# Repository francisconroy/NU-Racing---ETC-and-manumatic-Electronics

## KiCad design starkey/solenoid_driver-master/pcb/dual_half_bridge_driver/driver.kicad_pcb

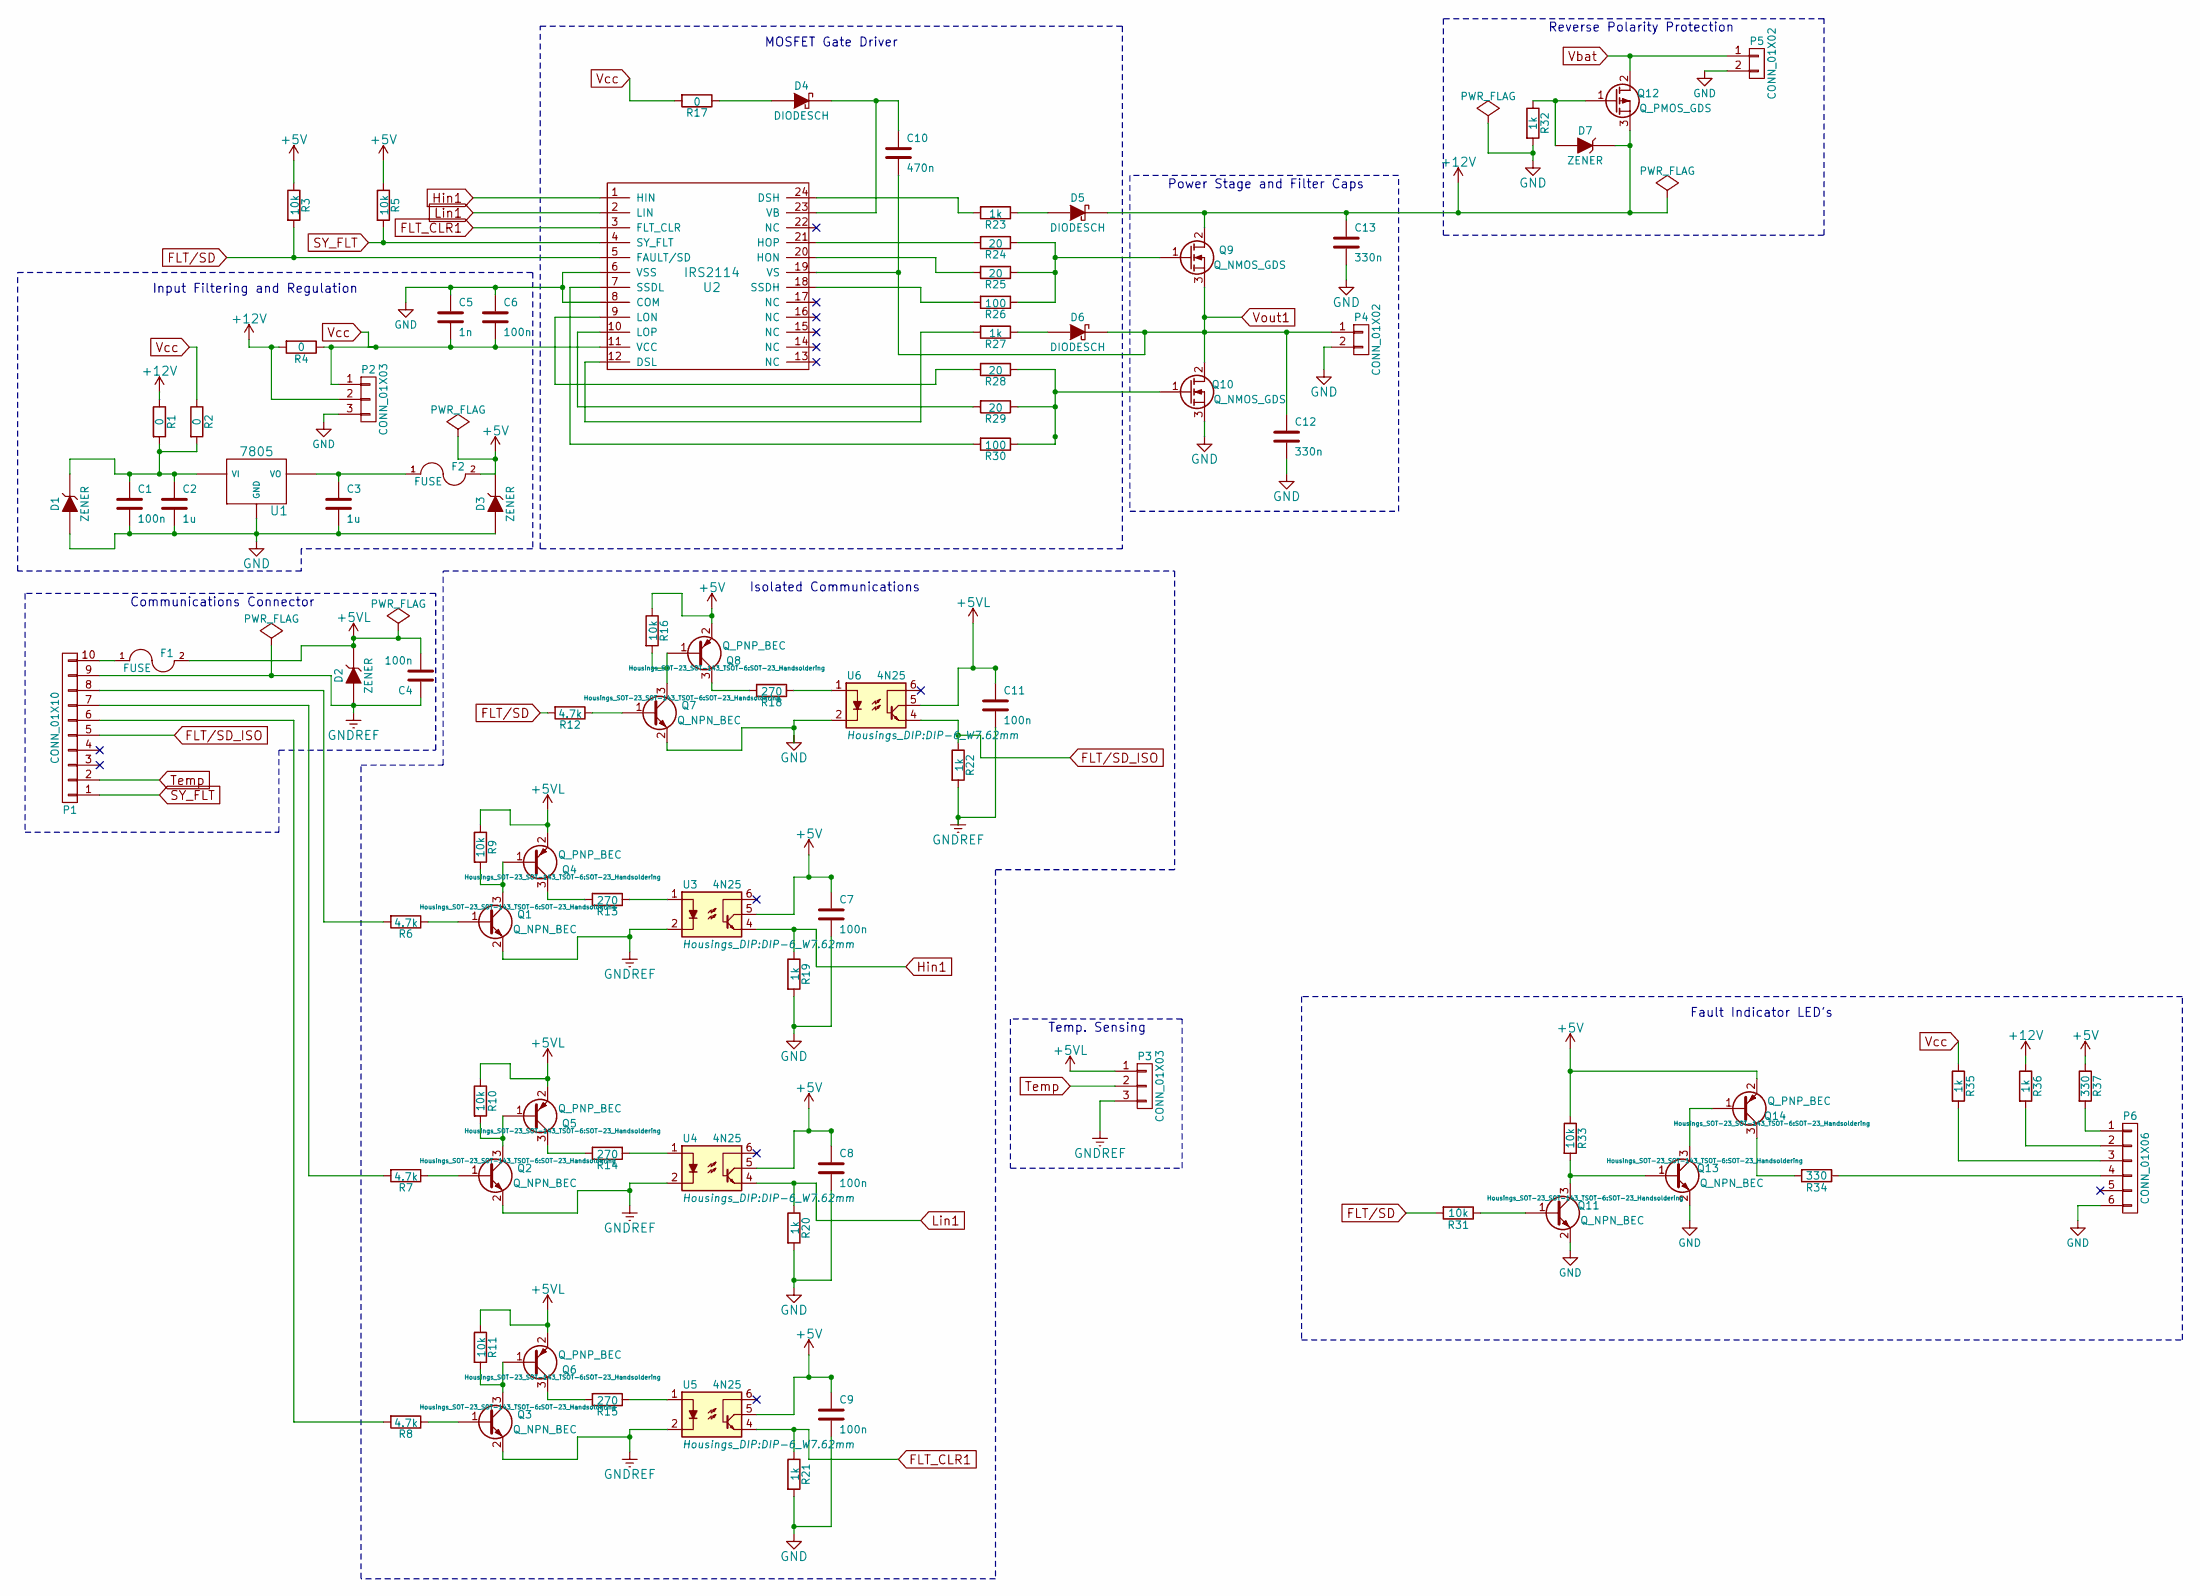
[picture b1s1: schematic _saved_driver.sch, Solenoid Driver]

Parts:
C1, C4, C6, C7, C8, C9, C11: 100n; C_1206_HandSoldering
C2, C3: 1u; C_1206_HandSoldering
C5: 1n; C_1206_HandSoldering
C10: 470n; C_1206_HandSoldering
C12: 330n; C_Rect_L32_W15_P27
C13: 330n; C_Rect_L18_W6_H12_P15
D1, D2, D3, D7: ZENER; SMD-1206_Pol
D4, D5, D6: DIODESCH; SMD-1206_Pol
F1, F2: FUSE; R_1206_HandSoldering
P1: CONN_01X10; Pin_Header_Straight_1x10
P2, P3: CONN_01X03; Pin_Header_Straight_1x03
P4: CONN_01X02; Pin_Header_Straight_1x02
P5: CONN_01X02; Crimp_Connector_2
P6: CONN_01X06; Pin_Header_Straight_1x06
Q1, Q2, Q3, Q7, Q11, Q13: Q_NPN_BEC; SOT-23_Handsoldering
Q4, Q5, Q6, Q8, Q14: Q_PNP_BEC; SOT-23_Handsoldering
Q9, Q10: Q_NMOS_GDS; TO-247_Vertical_Neutral123
Q12: Q_PMOS_GDS; TO-220_Neutral123_Vertical
R1, R2, R4, R17: 0; R_1206_HandSoldering
R3, R5, R9, R10, R11, R16, R31, R33: 10k; R_1206_HandSoldering
R6, R7, R8, R12: 4.7k; R_1206_HandSoldering
R13, R14, R15, R18: 270; R_1206_HandSoldering
R19, R20, R21, R22, R23, R27, R32, R35, R36: 1k; R_1206_HandSoldering
R24, R25, R28, R29: 20; R_1206_HandSoldering
R26, R30: 100; R_1206_HandSoldering
R34, R37: 330; R_1206_HandSoldering
U1: 7805; D-Pak_TO252AA
U2: IRS2114; SSOP-24_5.3x8.2mm_Pitch0.65mm
U3, U4, U5, U6: 4N25; DIP-6_W7.62mm

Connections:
+5V: C7.1, C8.1, C9.1, D3.2 (K), F2.2, Q8.2 (E), Q14.2 (E), R3.1, R5.1, R16.1, R33.1, R37.1, U3.5, U4.5, U5.5; also elsewhere on the board
+5VL: C4.2, C11.1, D2.2 (K), F1.2, P3.1, Q4.2 (E), Q5.2 (E), Q6.2 (E), R9.1, R10.1, R11.1, U6.5
+12V: C13.1, D5.2 (K), D7.2 (K), P2.2, Q9.2 (D), Q12.3 (S), R1.1, R4.2, R36.1
FLT/SD: R3.2, R12.2, R31.2, U2.5 (FAULT/SD)
FLT/SD_ISO: P1.5, R22.1, U6.4
FLT_CLR1: R21.1, U2.3 (FLT_CLR), U5.4
GNDREF: C4.1, C11.2, D2.1 (A), P1.9, P3.3, Q1.2 (E), Q2.2 (E), Q3.2 (E), R22.2, U3.2, U4.2, U5.2
Hin1: R19.1, U2.1 (HIN), U3.4
Lin1: R20.1, U2.2 (LIN), U4.4
unnamed: C1.1, C2.1, D1.2 (K), R1.2, R2.2, U1.1, U1.VI
unnamed: C3.1, F2.1, U1.3, U1.VO
unnamed: C10.1, D4.2 (K), U2.23 (VB)
unnamed: D4.1 (A), R17.1
unnamed: D5.1 (A), R23.1
unnamed: D6.1 (A), R27.1
unnamed: D7.1 (A), Q12.1 (G), R32.1
unnamed: F1.1, P1.10
unnamed: P1.6, R8.2
unnamed: P1.7, R7.2
unnamed: P1.8, R6.2
unnamed: P6.1, R37.2
unnamed: P6.2, R36.2
unnamed: P6.3, R35.2
unnamed: P6.4, R34.1
unnamed: Q1.1 (B), R6.1
unnamed: Q1.3 (C), Q4.1 (B), R9.2
unnamed: Q2.1 (B), R7.1
unnamed: Q2.3 (C), Q5.1 (B), R10.2
unnamed: Q3.1 (B), R8.1
unnamed: Q3.3 (C), Q6.1 (B), R11.2
unnamed: Q4.3 (C), R13.2
unnamed: Q5.3 (C), R14.2
unnamed: Q6.3 (C), R15.2
unnamed: Q7.1 (B), R12.1
unnamed: Q7.3 (C), Q8.1 (B), R16.2
unnamed: Q8.3 (C), R18.2
unnamed: Q9.1 (G), R24.1, R25.1, R26.1
unnamed: Q10.1 (G), R28.1, R29.1, R30.1
unnamed: Q11.1 (B), R31.1
unnamed: Q11.3 (C), Q13.1 (B), R33.2
unnamed: Q13.3 (C), Q14.1 (B)
unnamed: Q14.3 (C), R34.2
unnamed: R13.1, U3.1
unnamed: R14.1, U4.1
unnamed: R15.1, U5.1
unnamed: R18.1, U6.1
unnamed: R23.2, U2.24 (DSH)
unnamed: R24.2, U2.21 (HOP)
unnamed: R25.2, U2.20 (HON)
unnamed: R26.2, U2.18 (SSDH)
unnamed: R27.2, U2.12 (DSL)
unnamed: R28.2, U2.9 (LON)
unnamed: R29.2, U2.10 (LOP)
unnamed: R30.2, U2.7 (SSDL)
SY_FLT: P1.1, R5.2, U2.4 (SY_FLT)
Temp: P1.2, P3.2
Vbat: P5.1, Q12.2 (D)
Vcc: C5.2, C6.2, P2.1, R2.1, R4.1, R17.2, R35.1, U2.11 (VCC)
Vout1: C10.2, C12.1, D6.2 (K), P4.1, Q9.3 (S), Q10.2 (D), U2.19 (VS)

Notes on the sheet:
Fault Indicator LED's
MOSFET Gate Driver
Power Stage and Filter Caps
Reverse Polarity Protection
Input Filtering and Regulation
Isolated Communications
Communications Connector
Temp. Sensing

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
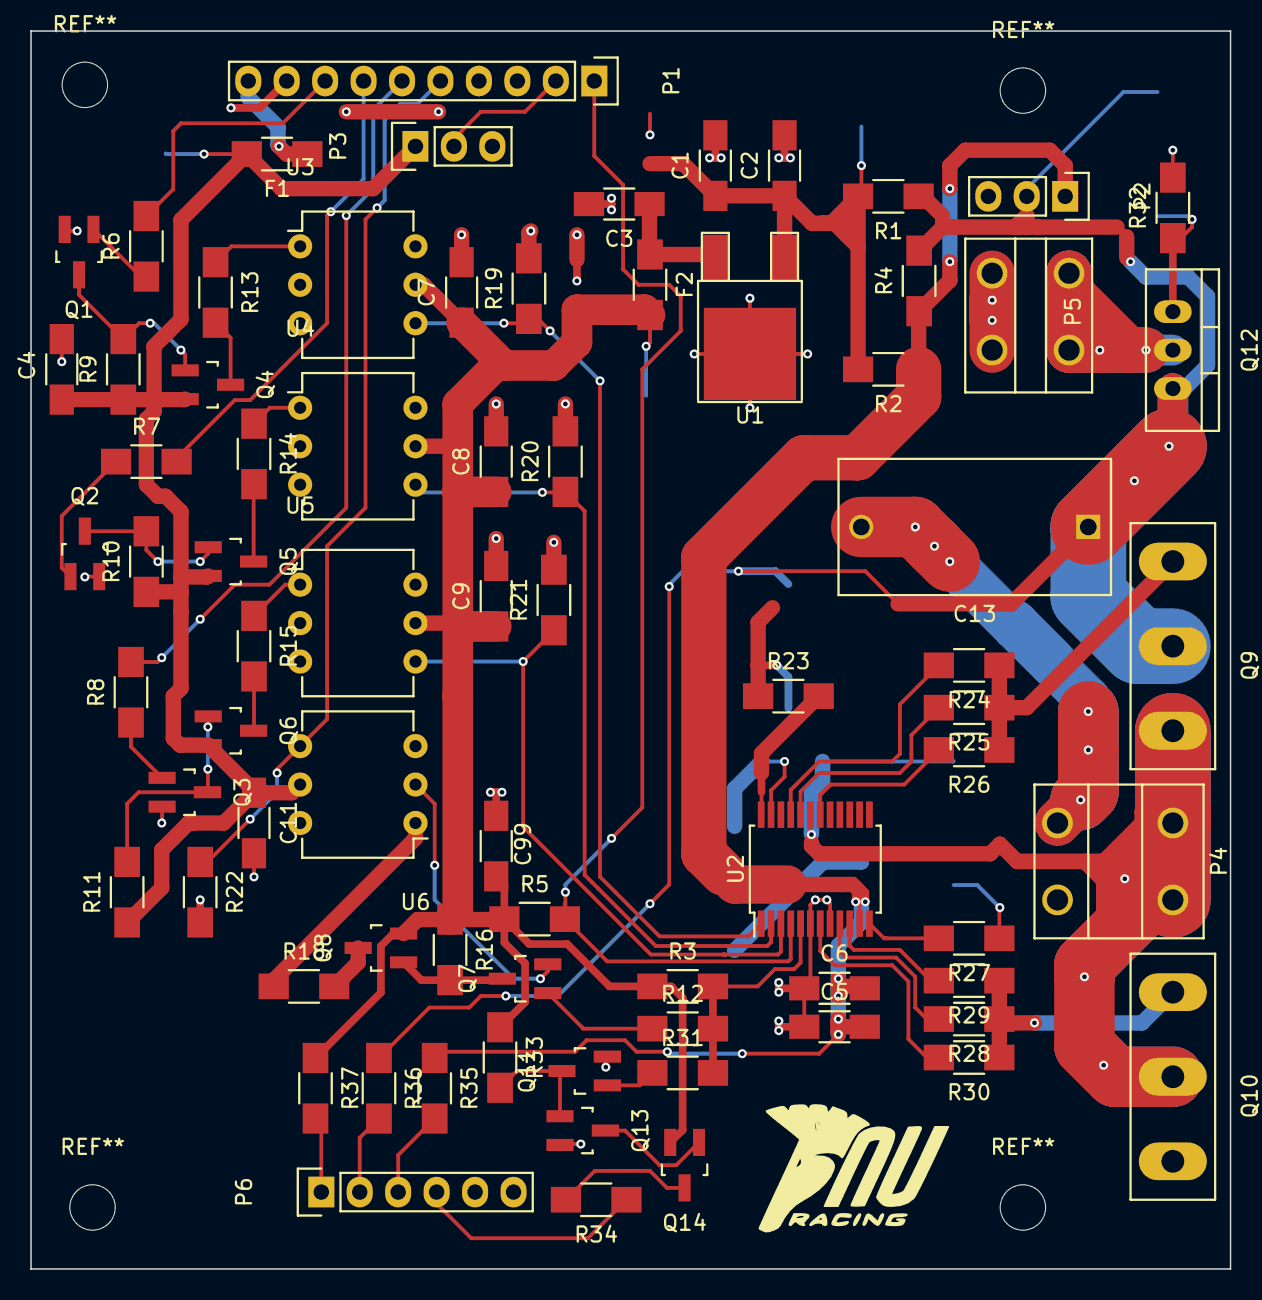
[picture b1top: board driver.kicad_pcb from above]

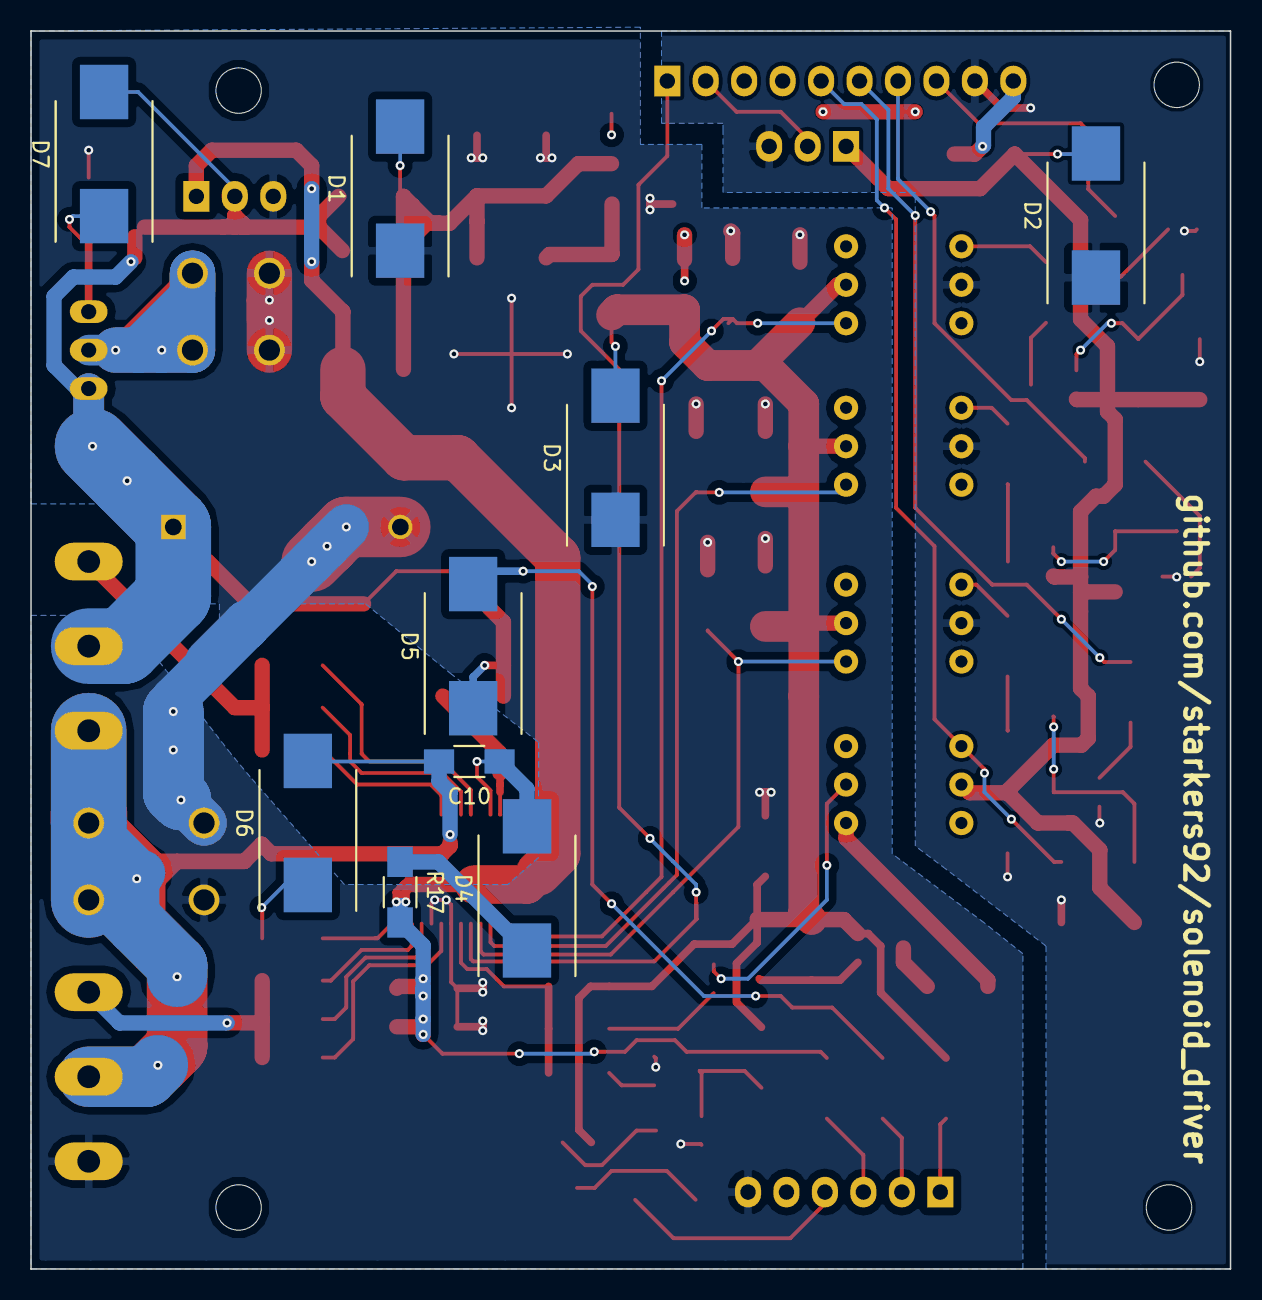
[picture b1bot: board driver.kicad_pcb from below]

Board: 2 copper layers, 79.2 x 81.8 mm, 85 parts (9 on the bottom side), 61 nets.

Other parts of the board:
C99: C_1206_HandSoldering

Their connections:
+5V: C99.1; also elsewhere on the board

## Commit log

2015-08-13 Initial commit to repo
    Commit ETC PCB layout as version 1.0
2015-08-16 v1.0 of ETC board complete
    initial work on GS board underway too
2015-08-19 finish version 1.0 of GS board
    yay!
2015-09-01 Versions of the board which went to the fab house
    Updating BOMS for component ordering
2015-09-01 more BOM work
    working on the BOMs
2015-09-22 update
    make pdf
2015-09-28 update for hardware construction
2015-10-09 update for connectors
    upd
2015-10-15 update connectors
2015-11-01 update at harness master
    update at harness master
2015-11-08 Update PINouts for testing
    update pinouts for new software developments
2015-11-25 update to fix reverse polarity protection
    FLIP DS on FET, only done on ETC schematic
2015-12-01 Updates with wiring updates
    Woop
2015-12-18 update before comp
    Updates
